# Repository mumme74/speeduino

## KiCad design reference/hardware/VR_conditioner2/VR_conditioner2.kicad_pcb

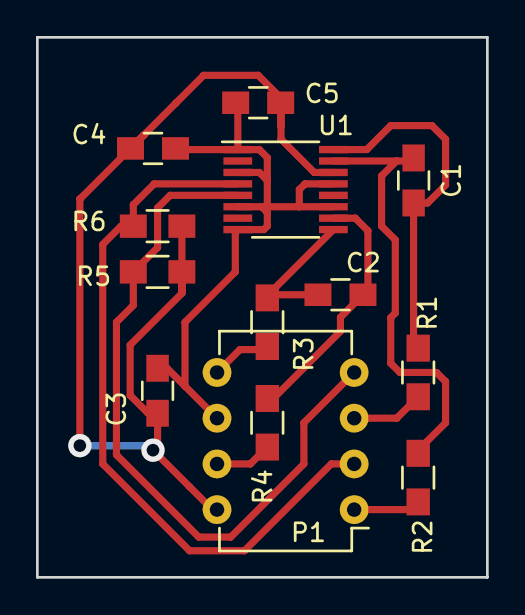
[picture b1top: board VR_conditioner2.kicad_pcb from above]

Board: 2 copper layers, 25.0 x 30.0 mm, 13 parts (0 on the bottom side), 12 nets.

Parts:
C1, C2: 1n; C_0805_HandSoldering
C3: 1u; C_0805_HandSoldering
C4: 0.1u; C_0805_HandSoldering
C5: 10n; C_0805_HandSoldering
P1: dil8; DIP-8_W7.62mm
R1, R2, R3, R4, R5, R6: 10k; R_0805_HandSoldering
U1: MAX9926; QSOP-16_3.9x4.9mm_Pitch0.635mm

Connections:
/+5v: C3.1, C4.1, C5.1, P1.8, R5.1, R6.1, U1.14
/gnd: C3.2, C4.2, C5.2, P1.6, U1.1, U1.3, U1.6, U1.8, U1.11, U1.13
/in1+: C1.2, R1.2, U1.16
/in1-: C1.1, R2.2, U1.15
/in2+: C2.2, R3.2, U1.9
/in2-: C2.1, R4.2, U1.10
/out1: P1.2, R6.2, U1.4
/out2: P1.4, R5.2, U1.5
/vr1+: P1.3, R1.1
/vr1-: P1.1, R2.1
/vr2+: P1.5, R3.1
/vr2-: P1.7, R4.1

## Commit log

2015-01-04 adding include guards and some changes to the code
2015-01-04 first run to make it more or less compile with teensy in eclipse arduino plugin next up Scheduler...
2015-01-04 compiler warning fix
2015-02-14 include header files
2015-02-17 Added Sequential indicator to Tuner Studio
2015-02-17 Revert pull from upstrem to "Make misfire cyl detection a bit more stable"
    This reverts commit aa8f6af3b57d64131dfeefadc43f80e2e7fe28b7.
2015-02-17 Revert "Revert pull from upstrem to "Make misfire cyl detection a bit more stable""
    This reverts commit 16aa91691cc4dbd926957a998ba798dac287b7b3.
2015-02-17 Revert "Merge remote-tracking branch 'upstream/master' into sequential"
    This reverts commit 2f23534ff8cca152322a4b3b9d92d8d6213a6752, reversing
    changes made to aa8f6af3b57d64131dfeefadc43f80e2e7fe28b7.
2015-02-17 Bugfix wrong logic when selecting fuel
2015-02-18 Fix a charset issue, eclipse saved the file with utf8
2017-01-22 Add/change some VR conditioner (single sided pcb)
